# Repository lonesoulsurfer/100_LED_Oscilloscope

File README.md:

# 100 LED Oscilloscope

This is a simple oscilloscope with a display of 100 LEDs (10 × 10). The resolution is too low for measurements, but it is very good to see audio waveforms from a microphone.

## Build guide and video

- Step-by-step build guide on Instructables: [100 LED Oscilloscope](https://www.instructables.com/100-LED-Oscilloscope/)
- Video on YouTube: [100 LED Oscilloscope](https://youtu.be/FqV2W9gObf8)

## How it works

The circuit has 4 ICs:

| IC | Function |
|----|----------|
| 4017 decade counter | Selects the LED columns |
| LM3914 LED driver | Selects the LED rows from the signal level |
| 555 timer | Makes the clock signal |
| LM386 amplifier | Makes the input signal larger |

The LEDs are 5 mm square LEDs. Their flat tops make it easy to keep them straight and in line when you solder them.

## What you need

- All parts are in the [parts list](LED%20Oscilloscope%20-%20Parts%20List.pdf).
- Schematics: [version 1](LED%20Oscilloscope%20V1%20Schematic.pdf) and [version 2](LED%20Oscilloscope%20V2%20Schematic%20.pdf).
- The Gerber files for the PCB are in [Gerber files](Gerber%20files/). You can send them to a PCB maker. Each version has an option for a fine horizontal control potentiometer.

## Files in this repository

| Folder or file | Contents |
|----------------|----------|
| `Eagle Schematic and board/` | Eagle files for versions 1 and 2 |
| `Gerber files/` | Gerber files for versions 1 and 2, ready to order |
| `Inkscape - Front Panel/` | Front panel design (SVG and PDF) |
| `LED Oscilloscope - Parts List.pdf` | Parts list |
| `LED Oscilloscope V1 Schematic.pdf` | Schematic, version 1 |
| `LED Oscilloscope V2 Schematic .pdf` | Schematic, version 2 |

## Credits

- Based on the [LED oscilloscope with 100 LEDs](https://www.eddybergman.com/2017/10/led-oscilloscope-with-100-leds.html) by Eddy Bergman.
- PCB and build: Marcus ([lonesoulsurfer](https://github.com/lonesoulsurfer)).

## Support

Do you like this project? You can support my work on [GitHub Sponsors](https://github.com/sponsors/lonesoulsurfer).

## Licence

This project uses the [CERN Open Hardware Licence v2, Strongly Reciprocal](LICENSE) (CERN-OHL-S-2.0). Copyright (c) 2025 Marcus (lonesoulsurfer).

You can make, change and sell boards from these files. If you share or sell a changed design, you must also share the changed design files under the same licence.

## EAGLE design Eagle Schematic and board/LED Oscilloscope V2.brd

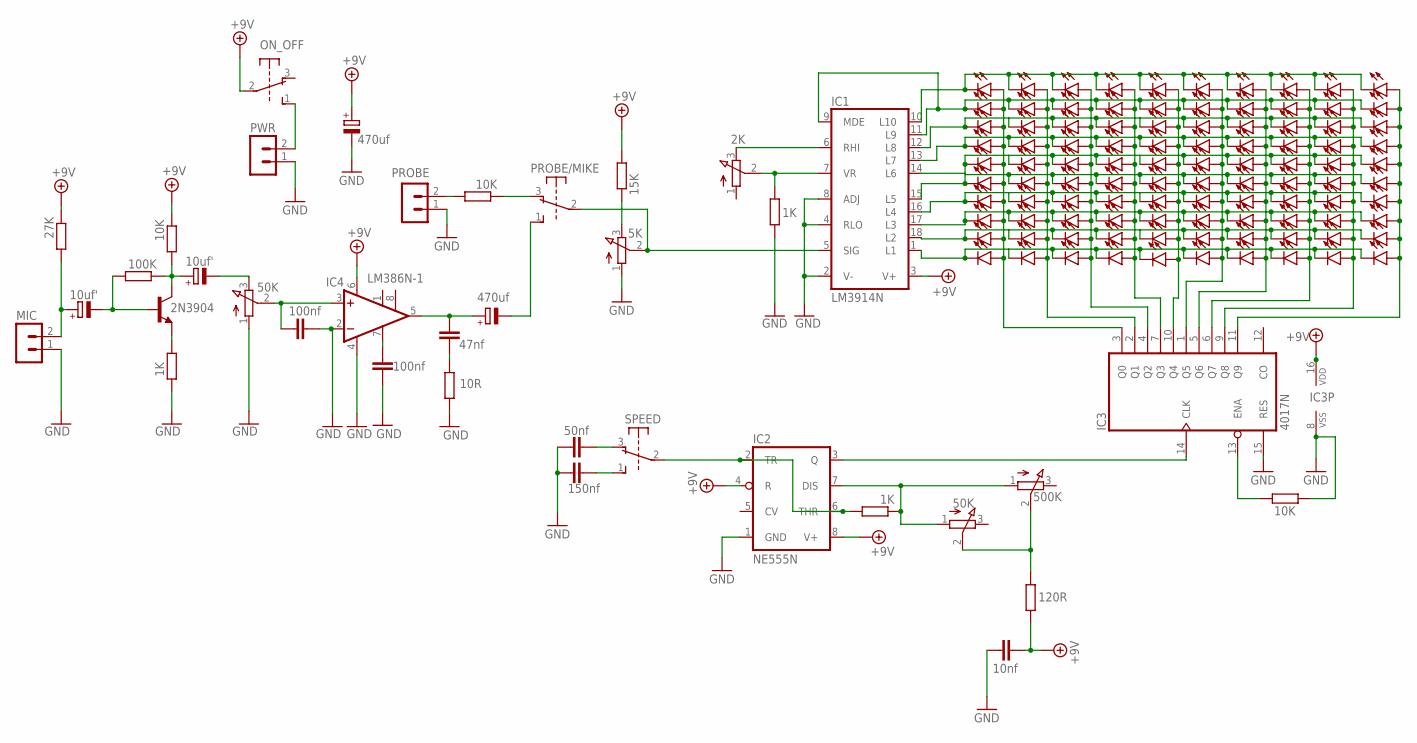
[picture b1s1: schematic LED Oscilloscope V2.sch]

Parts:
C1: 10nf; C050-024X044
C2: 50nf; C050-024X044
C3: 150nf; C050-024X044
C4, C10: 470uf; E2,5-6
C5, C8: 100nf; C050-024X044
C6, C7: 10uf'; E2-5
C9: 47nf; C050-024X044
FINE: 2K; EVUF
HORIZONTAL: 500K; EVUF
HOR_FINE: 50K; EVUF
IC1: LM3914N; DIL18
IC2: NE555N; DIL08
IC3: 4017N; DIL16
IC4: LM386N-1; DIL08
LED1, LED2, LED3, LED4, LED5, LED6, LED7, LED8, LED9, LED10, LED11, LED12, LED13, LED14, LED15, LED16, LED17, LED18, LED19, LED20, LED21, LED22, LED23, LED24, LED25, LED26, LED27, LED28, LED29, LED30, LED31, LED32, LED33, LED34, LED35, LED36, LED37, LED38, LED39, LED40, LED41, LED42, LED43, LED44, LED45, LED46, LED47, LED48, LED49, LED50, LED51, LED52, LED53, LED54, LED55, LED56, LED57, LED58, LED59, LED60, LED61, LED62, LED63, LED64, LED65, LED66, LED67, LED68, LED69, LED70, LED71, LED72, LED73, LED74, LED75, LED76, LED77, LED78, LED79, LED80, LED81, LED82, LED83, LED84, LED85, LED86, LED87, LED88, LED89, LED90, LED91, LED92, LED93, LED94, LED95, LED96, LED97, LED98, LED99, LED100: LED5MM
MIC: B2B-PH-K-S
ON_OFF: SWITCH-6PIN
PROBE: B2B-PH-K-S
PROBE/MIKE: SWITCH-6PIN
PWR: B2B-PH-K-S
R2, R3, R13: 1K; 0207/10
R5: 120R; 0207/10
R7: 15K; 0207/10
R8, R9, R11: 10K; 0207/10
R10: 10R; 0207/10
R12: 100K; 0207/10
R14: 27K; 0207/10
SPEED: SWITCH-6PIN
STENGTH: 50K; EVUF
T1: 2N3904; TO92
VERTICAL: 5K; EVUF

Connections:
+9V: C1.2, C4.+, IC1.3 (V+), IC2.4 (R), IC2.8 (V+), IC3.16 (VDD), IC4.6 (VS), ON_OFF.2, R5.2, R7.2, R11.1, R14.1
GND: C1.1, C2.2, C3.2, C4.-, C5.1, C8.2, IC1.2 (V-), IC1.4 (RLO), IC1.8 (ADJ), IC2.1 (GND), IC3.8 (VSS), IC3.15 (RES), IC4.2 (-IN), IC4.4 (GND), MIC.1, PROBE.1, PWR.1, R2.1, R9.1, R10.2, R13.1, STENGTH.1 (A), VERTICAL.1 (A)
unnamed: FINE.2 (S), IC1.7 (VR), R2.2
unnamed: FINE.3 (E), IC1.6 (RHI)
unnamed: IC2.2 (TR), IC2.6 (THR), R3.2, SPEED.2
unnamed: HORIZONTAL.2 (S), HOR_FINE.2 (S), R5.1
unnamed: C2.1, SPEED.3 (O)
unnamed: C3.1, SPEED.1 (S)
unnamed: PROBE/MIKE.3 (O), R8.1
unnamed: IC1.5 (SIG), PROBE/MIKE.2, VERTICAL.2 (S)
unnamed: R7.1, VERTICAL.3 (E)
unnamed: PROBE.2, R8.2
unnamed: IC1.10 (L10), LED1.K (C), LED2.K (C), LED3.K (C), LED4.K (C), LED5.K (C), LED6.K (C), LED7.K (C), LED8.K (C), LED9.K (C), LED10.K (C)
unnamed: IC1.9 (MDE), IC1.11 (L9), LED11.K (C), LED12.K (C), LED13.K (C), LED14.K (C), LED15.K (C), LED16.K (C), LED17.K (C), LED18.K (C), LED19.K (C), LED20.K (C)
unnamed: IC1.12 (L8), LED21.K (C), LED22.K (C), LED23.K (C), LED24.K (C), LED25.K (C), LED26.K (C), LED27.K (C), LED28.K (C), LED29.K (C), LED30.K (C)
unnamed: IC1.13 (L7), LED31.K (C), LED32.K (C), LED33.K (C), LED34.K (C), LED35.K (C), LED36.K (C), LED37.K (C), LED38.K (C), LED39.K (C), LED40.K (C)
unnamed: IC1.14 (L6), LED41.K (C), LED42.K (C), LED43.K (C), LED44.K (C), LED45.K (C), LED46.K (C), LED47.K (C), LED48.K (C), LED49.K (C), LED50.K (C)
unnamed: IC1.15 (L5), LED51.K (C), LED52.K (C), LED53.K (C), LED54.K (C), LED55.K (C), LED56.K (C), LED57.K (C), LED58.K (C), LED59.K (C), LED60.K (C)
unnamed: IC1.16 (L4), LED61.K (C), LED62.K (C), LED63.K (C), LED64.K (C), LED65.K (C), LED66.K (C), LED67.K (C), LED68.K (C), LED69.K (C), LED70.K (C)
unnamed: IC1.17 (L3), LED71.K (C), LED72.K (C), LED73.K (C), LED74.K (C), LED75.K (C), LED76.K (C), LED77.K (C), LED78.K (C), LED79.K (C), LED80.K (C)
unnamed: IC1.18 (L2), LED81.K (C), LED82.K (C), LED83.K (C), LED84.K (C), LED85.K (C), LED86.K (C), LED87.K (C), LED88.K (C), LED89.K (C), LED90.K (C)
unnamed: IC1.1 (L1), LED91.K (C), LED92.K (C), LED93.K (C), LED94.K (C), LED95.K (C), LED96.K (C), LED97.K (C), LED98.K (C), LED99.K (C), LED100.K (C)
unnamed: IC3.3 (Q0), LED1.A, LED11.A, LED21.A, LED31.A, LED41.A, LED51.A, LED61.A, LED71.A, LED81.A, LED91.A
unnamed: IC3.2 (Q1), LED2.A, LED12.A, LED22.A, LED32.A, LED42.A, LED52.A, LED62.A, LED72.A, LED82.A, LED92.A
unnamed: IC3.4 (Q2), LED3.A, LED13.A, LED23.A, LED33.A, LED43.A, LED53.A, LED63.A, LED73.A, LED83.A, LED93.A
unnamed: IC3.7 (Q3), LED4.A, LED14.A, LED24.A, LED34.A, LED44.A, LED54.A, LED64.A, LED74.A, LED84.A, LED94.A
unnamed: IC3.10 (Q4), LED5.A, LED15.A, LED25.A, LED35.A, LED45.A, LED55.A, LED65.A, LED75.A, LED85.A, LED95.A
unnamed: IC3.1 (Q5), LED6.A, LED16.A, LED26.A, LED36.A, LED46.A, LED56.A, LED66.A, LED76.A, LED86.A, LED96.A
unnamed: IC3.5 (Q6), LED7.A, LED17.A, LED27.A, LED37.A, LED47.A, LED57.A, LED67.A, LED77.A, LED87.A, LED97.A
unnamed: IC3.9 (Q8), LED9.A, LED19.A, LED29.A, LED39.A, LED49.A, LED59.A, LED69.A, LED79.A, LED89.A, LED99.A
unnamed: IC3.6 (Q7), LED8.A, LED18.A, LED28.A, LED38.A, LED48.A, LED58.A, LED68.A, LED78.A, LED88.A, LED98.A
unnamed: IC3.11 (Q9), LED10.A, LED20.A, LED30.A, LED40.A, LED50.A, LED60.A, LED70.A, LED80.A, LED90.A, LED100.A
unnamed: IC2.3 (Q), IC3.14 (CLK)
unnamed: C6.-, STENGTH.3 (E)
unnamed: HORIZONTAL.1 (A), HOR_FINE.1 (A), IC2.7 (DIS), R3.1
unnamed: C5.2, IC4.3 (+IN), STENGTH.2 (S)
unnamed: C6.+, R11.2, R12.2, T1.1 (C)
unnamed: C7.-, R12.1, T1.2 (B)
unnamed: R13.2, T1.3 (E)
unnamed: C8.1, IC4.7 (BYPASS)
unnamed: C9.1, C10.+, IC4.5 (OUT)
unnamed: C9.2, R10.1
unnamed: ON_OFF.1 (S), PWR.2
unnamed: C10.-, PROBE/MIKE.1 (S)
unnamed: C7.+, MIC.2, R14.2
unnamed: IC3.13 (ENA), R9.2

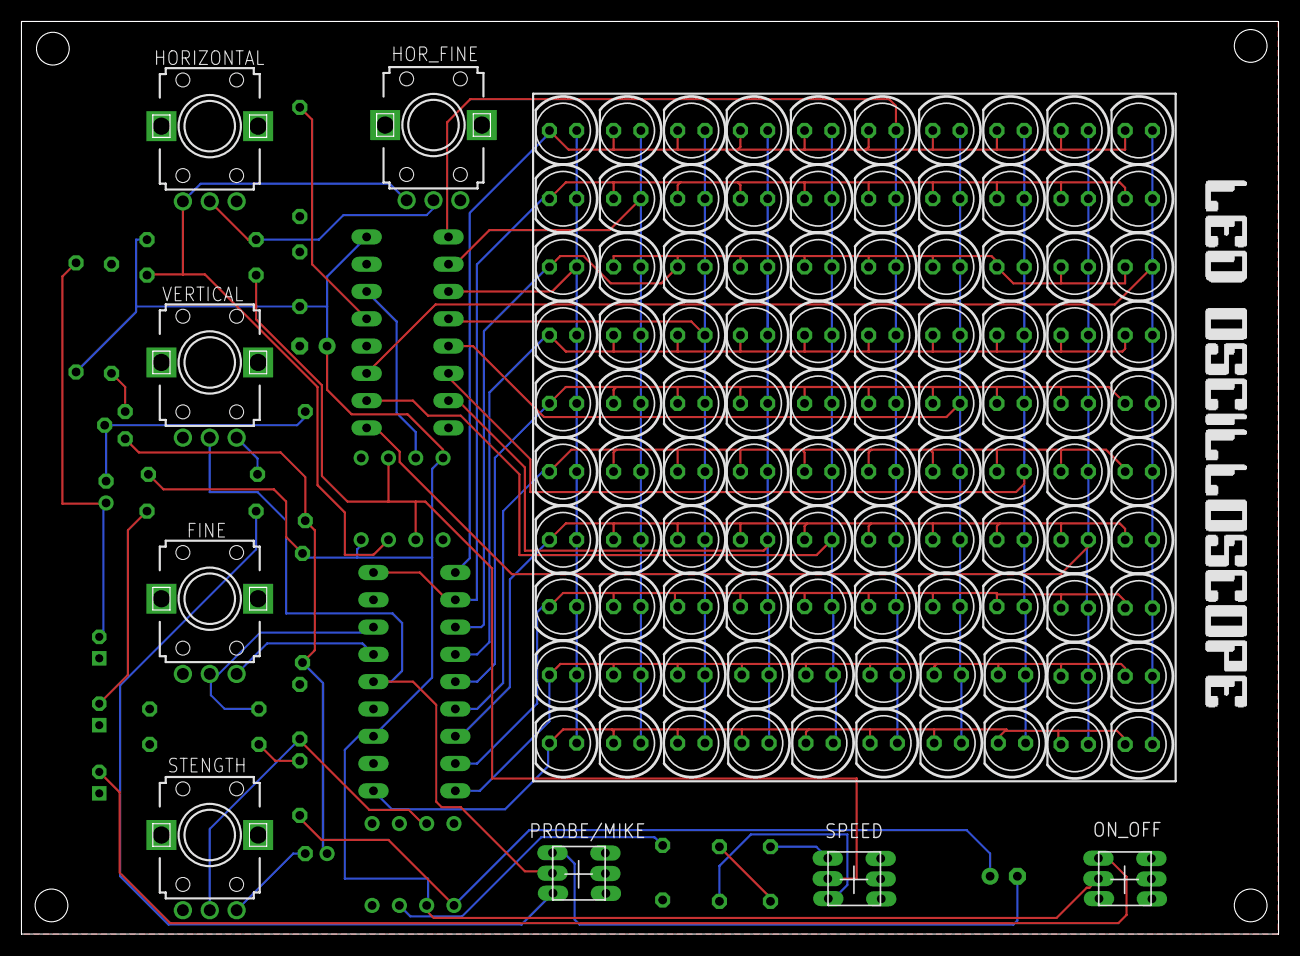
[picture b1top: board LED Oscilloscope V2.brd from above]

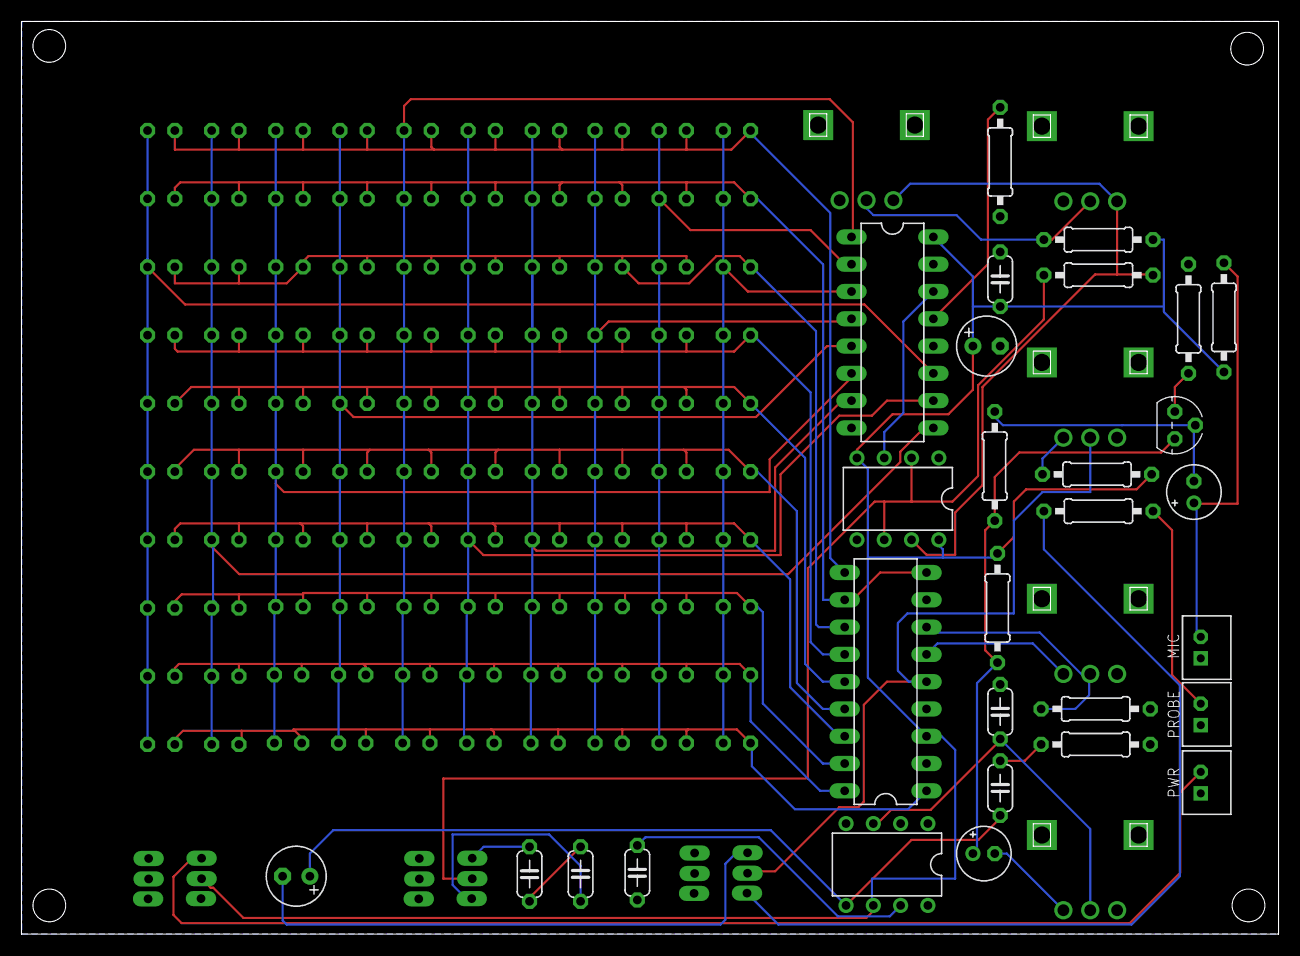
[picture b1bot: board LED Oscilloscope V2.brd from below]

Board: 2 copper layers, 117.0 x 85.0 mm, 137 parts (29 on the bottom side), 46 nets.
